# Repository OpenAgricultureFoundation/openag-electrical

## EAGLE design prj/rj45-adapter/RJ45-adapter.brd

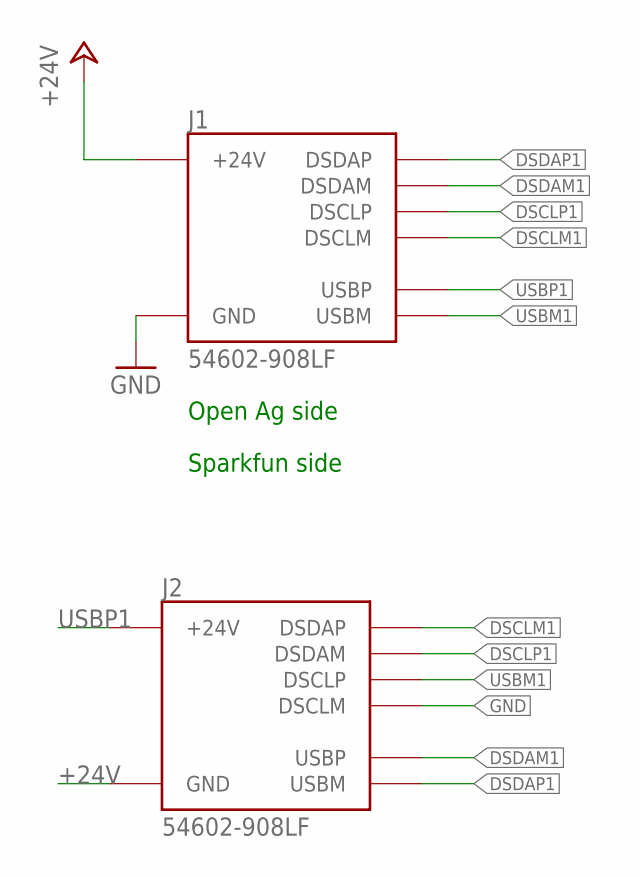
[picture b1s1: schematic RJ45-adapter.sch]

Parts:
J1, J2: 54602-908LF; OPENAG-V1-RJ45

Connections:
+24V: J1.24V(6) (+24V), J2.GND(3) (GND)
DSCLM1: J1.DSCLM(5) (DSCLM), J2.DSDAP(1) (DSDAP)
DSCLP1: J1.DSCLP(4) (DSCLP), J2.DSDAM(2) (DSDAM)
DSDAM1: J1.DSDAM(2) (DSDAM), J2.USBP(7) (USBP)
DSDAP1: J1.DSDAP(1) (DSDAP), J2.USBM(8) (USBM)
GND: J1.GND(3) (GND), J2.DSCLM(5) (DSCLM)
USBM1: J1.USBM(8) (USBM), J2.DSCLP(4) (DSCLP)
USBP1: J1.USBP(7) (USBP), J2.24V(6) (+24V)

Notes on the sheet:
Sparkfun side
Open Ag side

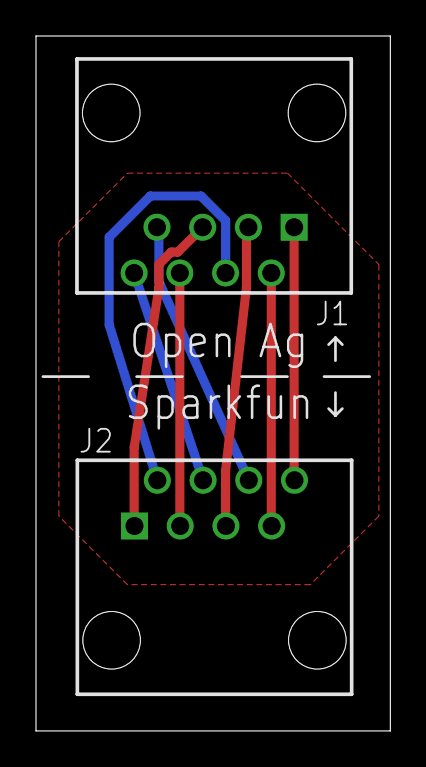
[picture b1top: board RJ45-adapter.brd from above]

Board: 2 copper layers, 19.7 x 38.6 mm, 3 parts (1 on the bottom side), 8 nets.

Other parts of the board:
ATTRIBUTES: DOCFIELD

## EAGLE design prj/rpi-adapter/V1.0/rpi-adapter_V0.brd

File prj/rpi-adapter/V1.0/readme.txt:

READ ME
Raspberry Pi to BBB socket i2c adapter 
THIS VERSION DOES NOT WORK! PLEASE SEE VERSION 2.0

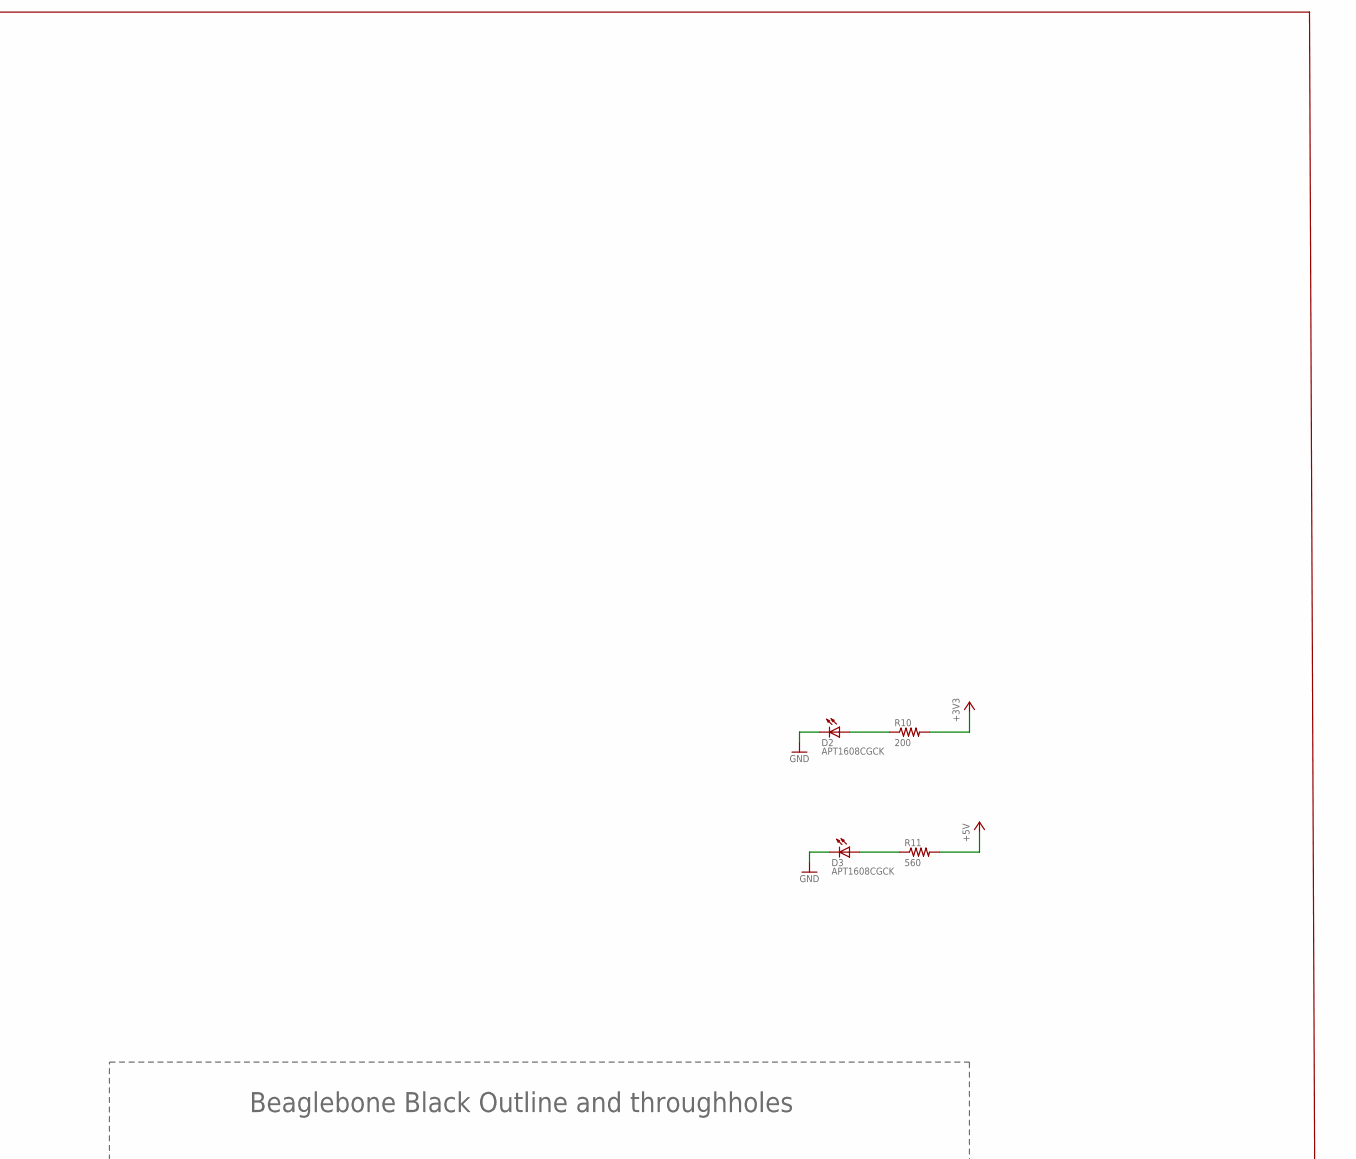
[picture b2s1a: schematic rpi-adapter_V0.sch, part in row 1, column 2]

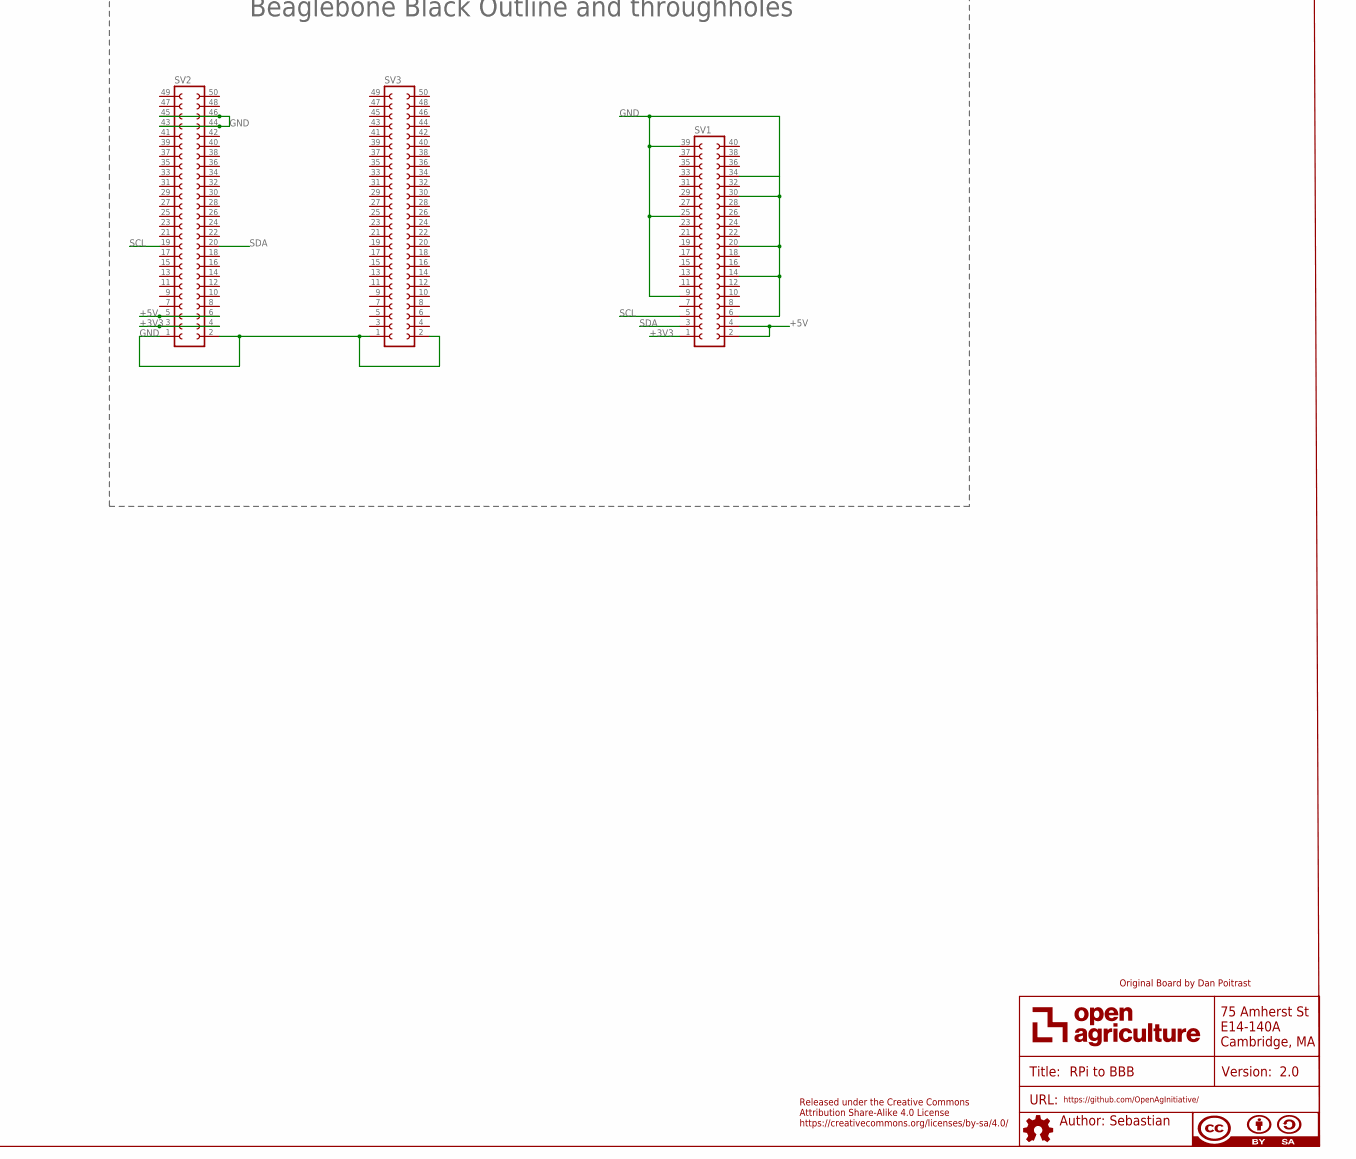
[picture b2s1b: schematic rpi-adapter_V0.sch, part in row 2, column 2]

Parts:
ATTRIBUTES: DOCFIELD
D2, D3: APT1608CGCK; CHIPLED_0603
R10: 200; RC0603N
R11: 560; RC0603N
SV1: FE20-2
SV2, SV3: FE25-2

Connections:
+3V3: R10.2, SV1.1, SV2.3, SV2.4
+5V: R11.2, SV1.2, SV1.4, SV2.5, SV2.6
GND: D2.C, D3.C, SV1.6, SV1.9, SV1.14, SV1.20, SV1.25, SV1.30, SV1.34, SV1.39, SV2.1, SV2.2, SV2.43, SV2.44, SV2.45, SV2.46, SV3.1, SV3.2
unnamed: D3.A, R11.1
unnamed: D2.A, R10.1
SCL: SV1.5, SV2.19
SDA: SV1.3, SV2.20

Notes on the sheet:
Original Board by Dan Poitrast
Released under the Creative Commons Attribution Share-Alike 4.0 License https://creativecommons.org/licenses/by-sa/4.0/
Beaglebone Black Outline and throughholes

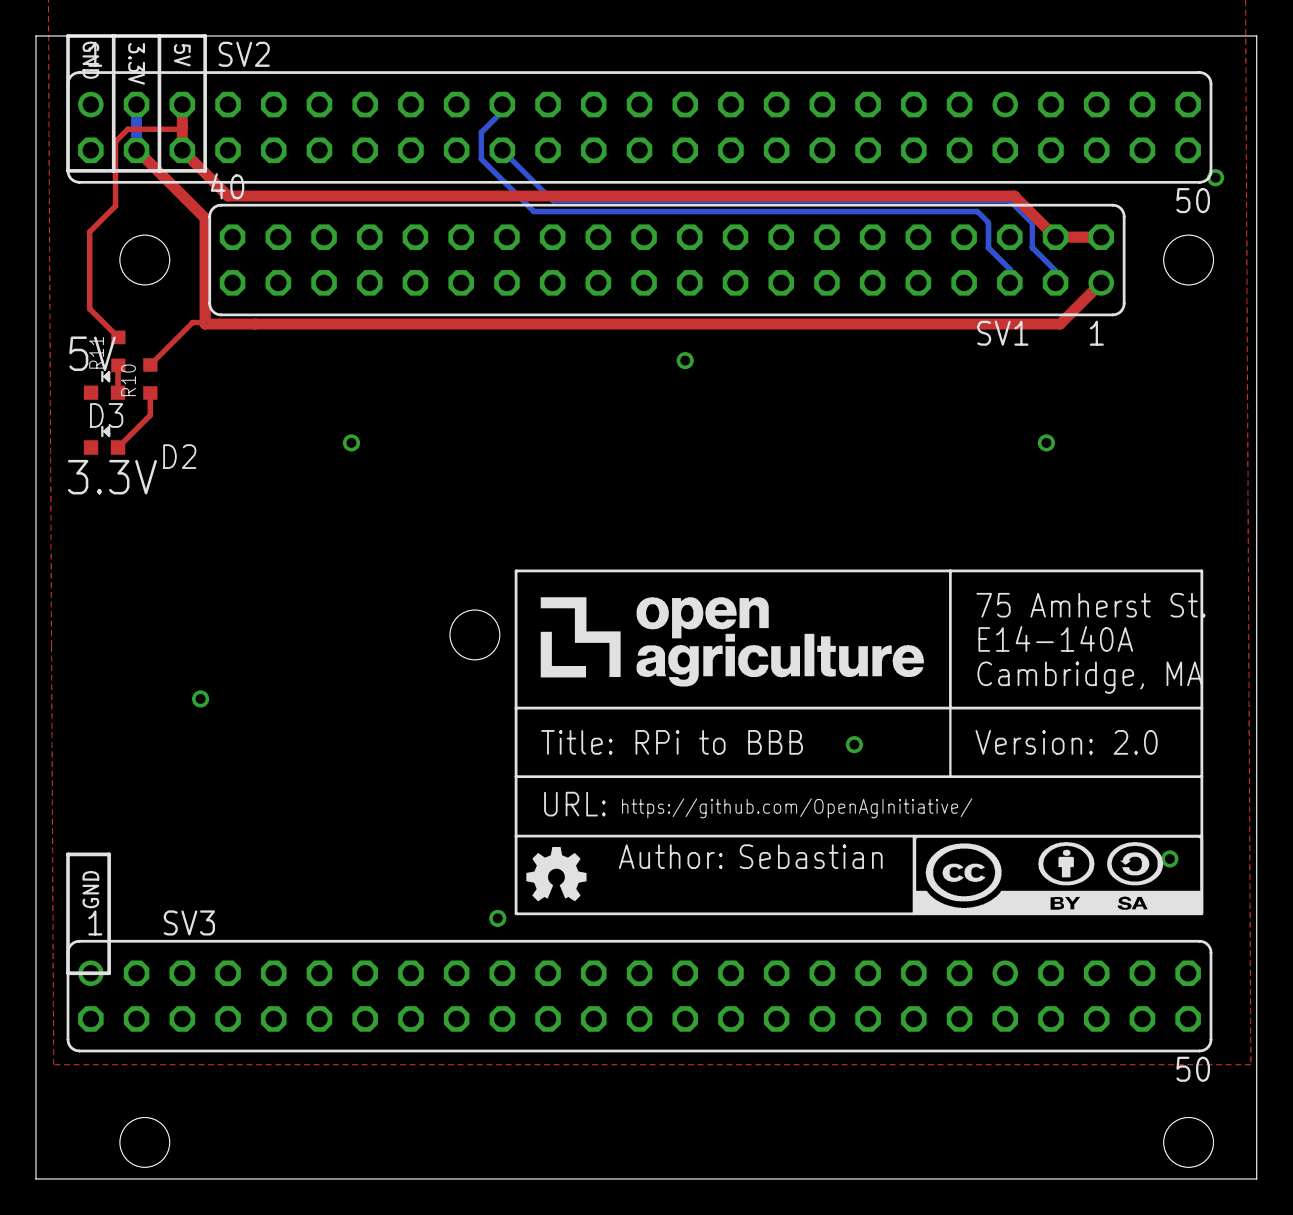
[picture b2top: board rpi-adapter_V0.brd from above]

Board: 2 copper layers, 67.8 x 63.5 mm, 8 parts (0 on the bottom side), 7 nets.

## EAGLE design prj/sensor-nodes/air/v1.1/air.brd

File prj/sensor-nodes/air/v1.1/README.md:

# Air Sensor Node v1.1
Sense air temperature, humidity and co2, redundently. Intended for evaluation purposes to determine sensors 
with best performance. Communicates over RJ45-dI2C for use with a nervous system board. Has option for standalone operation 
with wifi communication using a particle photon. Photon module has a 5v regulator enable to accomodate multiple power options. 
CO2 Sensors: T6713 and CCS811. Temperature / Humidity Sensors: SHT25 and HTU20DF.

### Contents
1. [Schematic](#schematic)
2. [Board](#board)
2. [Board Top](#board-top)
3. [Board Bottom](#board-bottom)
4. [Bill of Materials](air.csv)
5. [Gerber Files](air_sensor_node_v_1_1.zip)

### Schematic

### Board

### Board Top

### Board Bottom

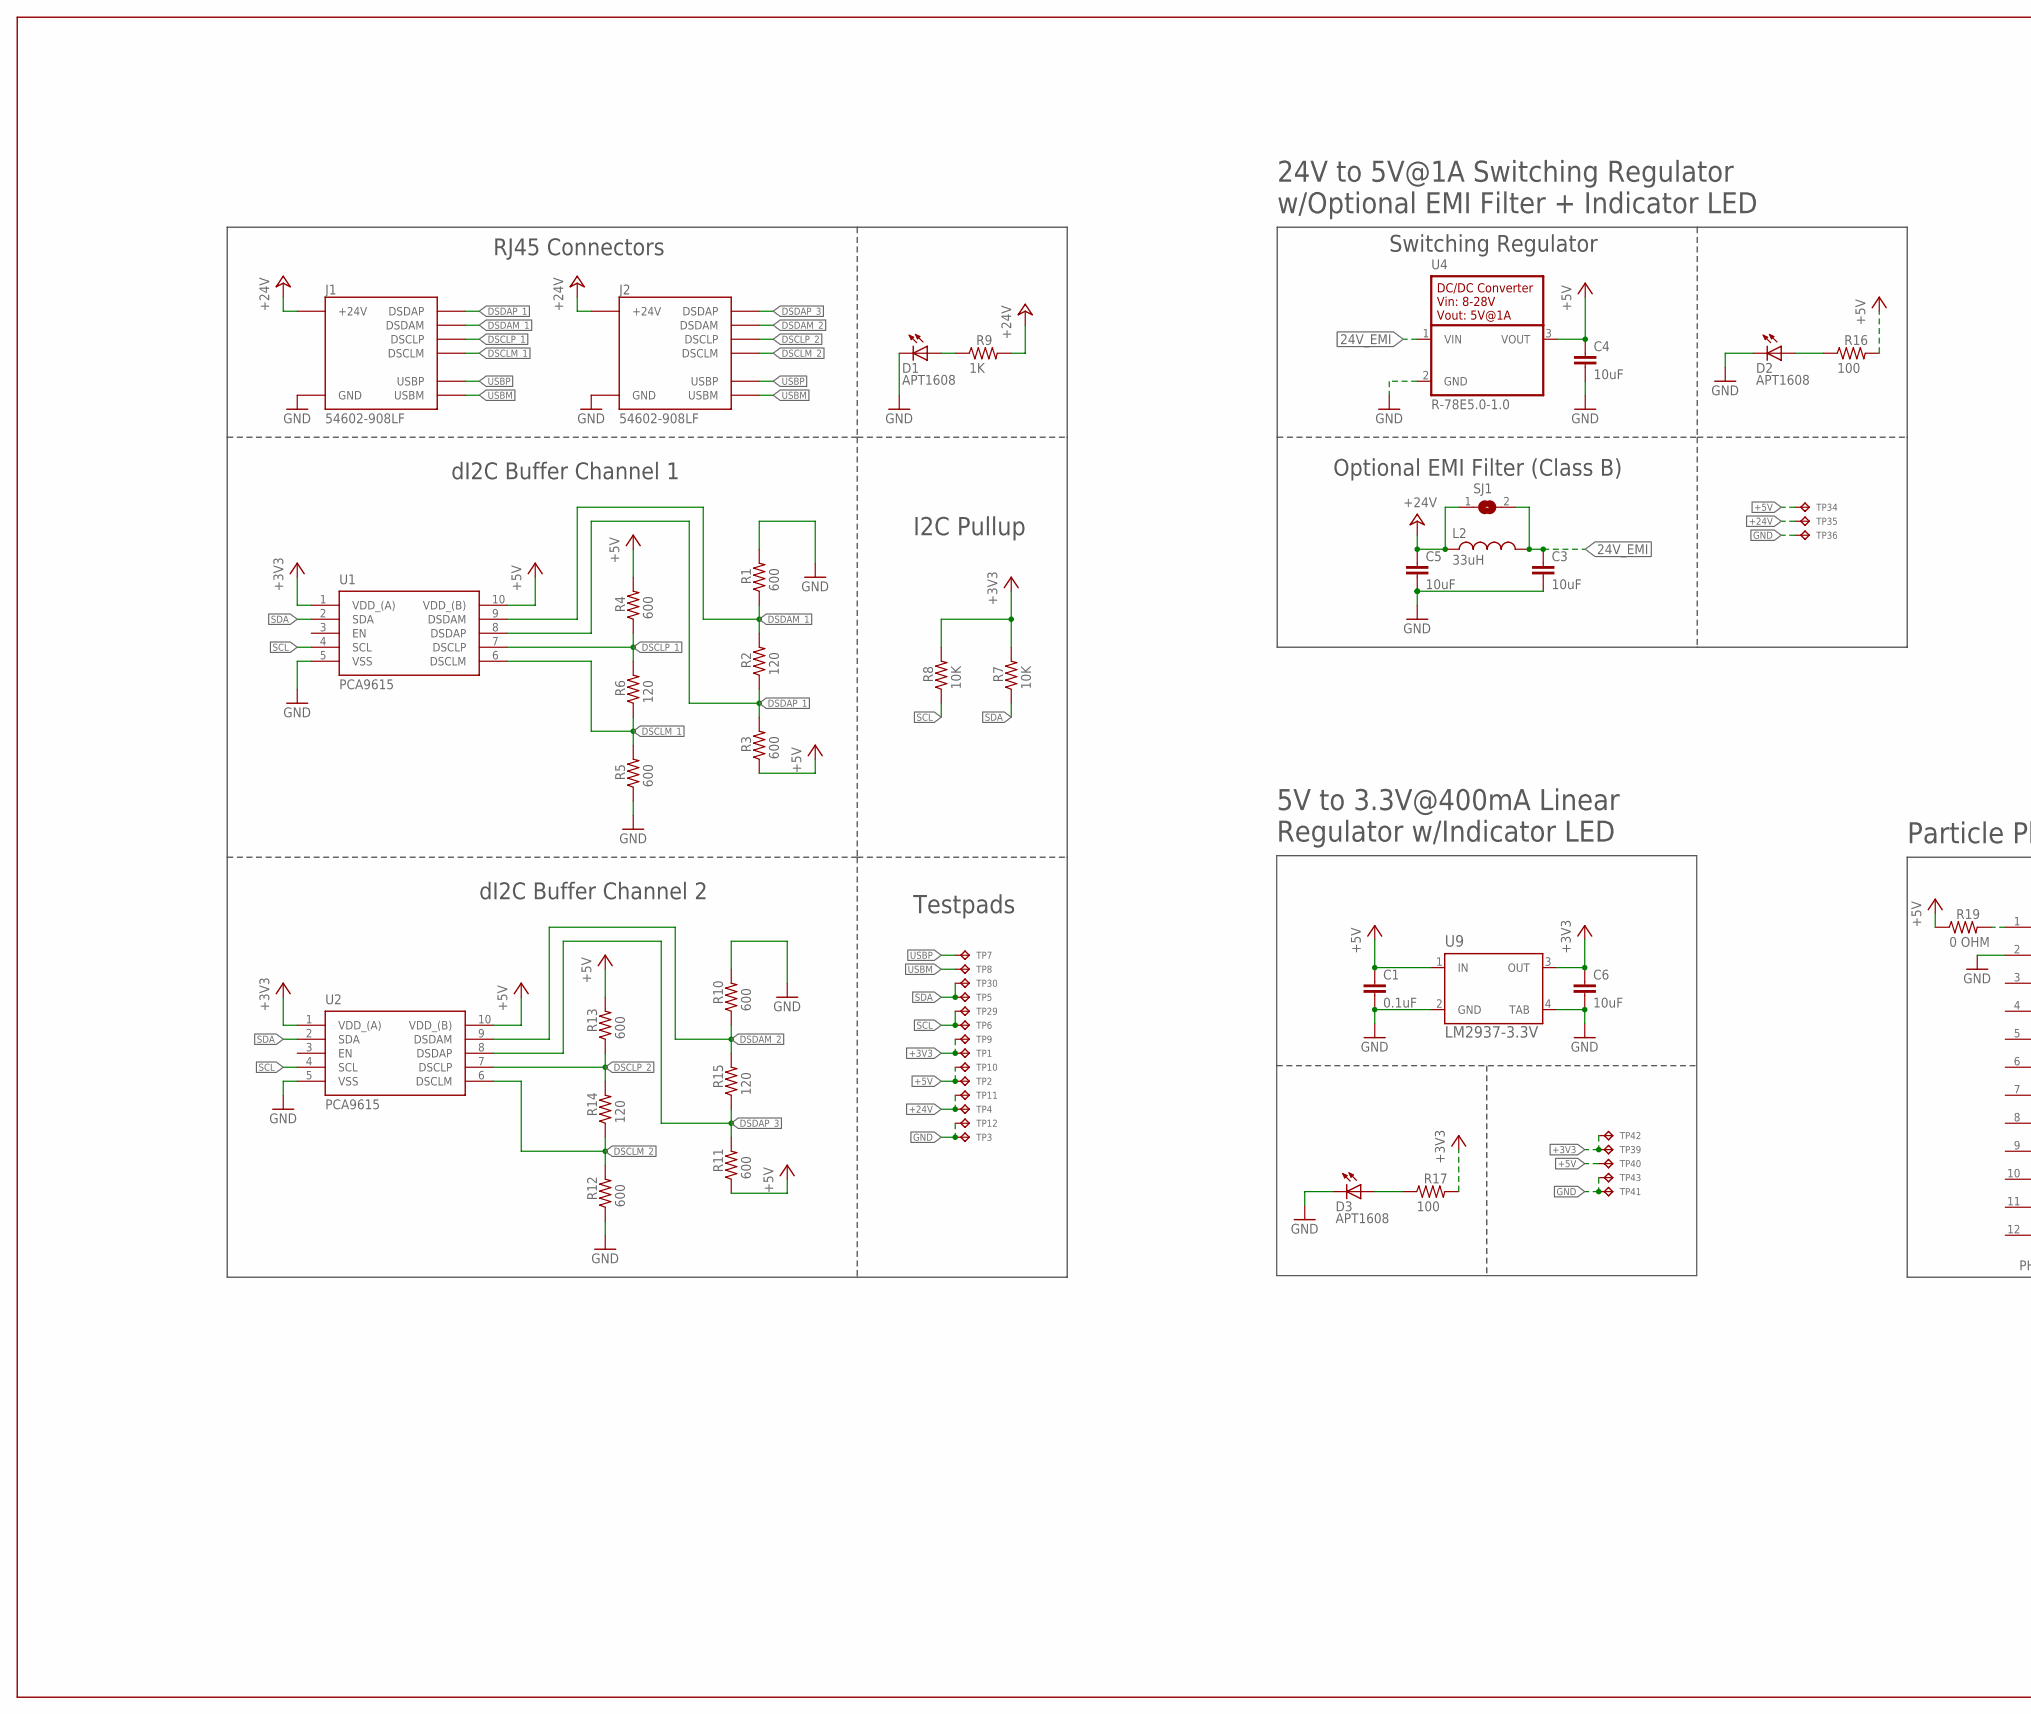
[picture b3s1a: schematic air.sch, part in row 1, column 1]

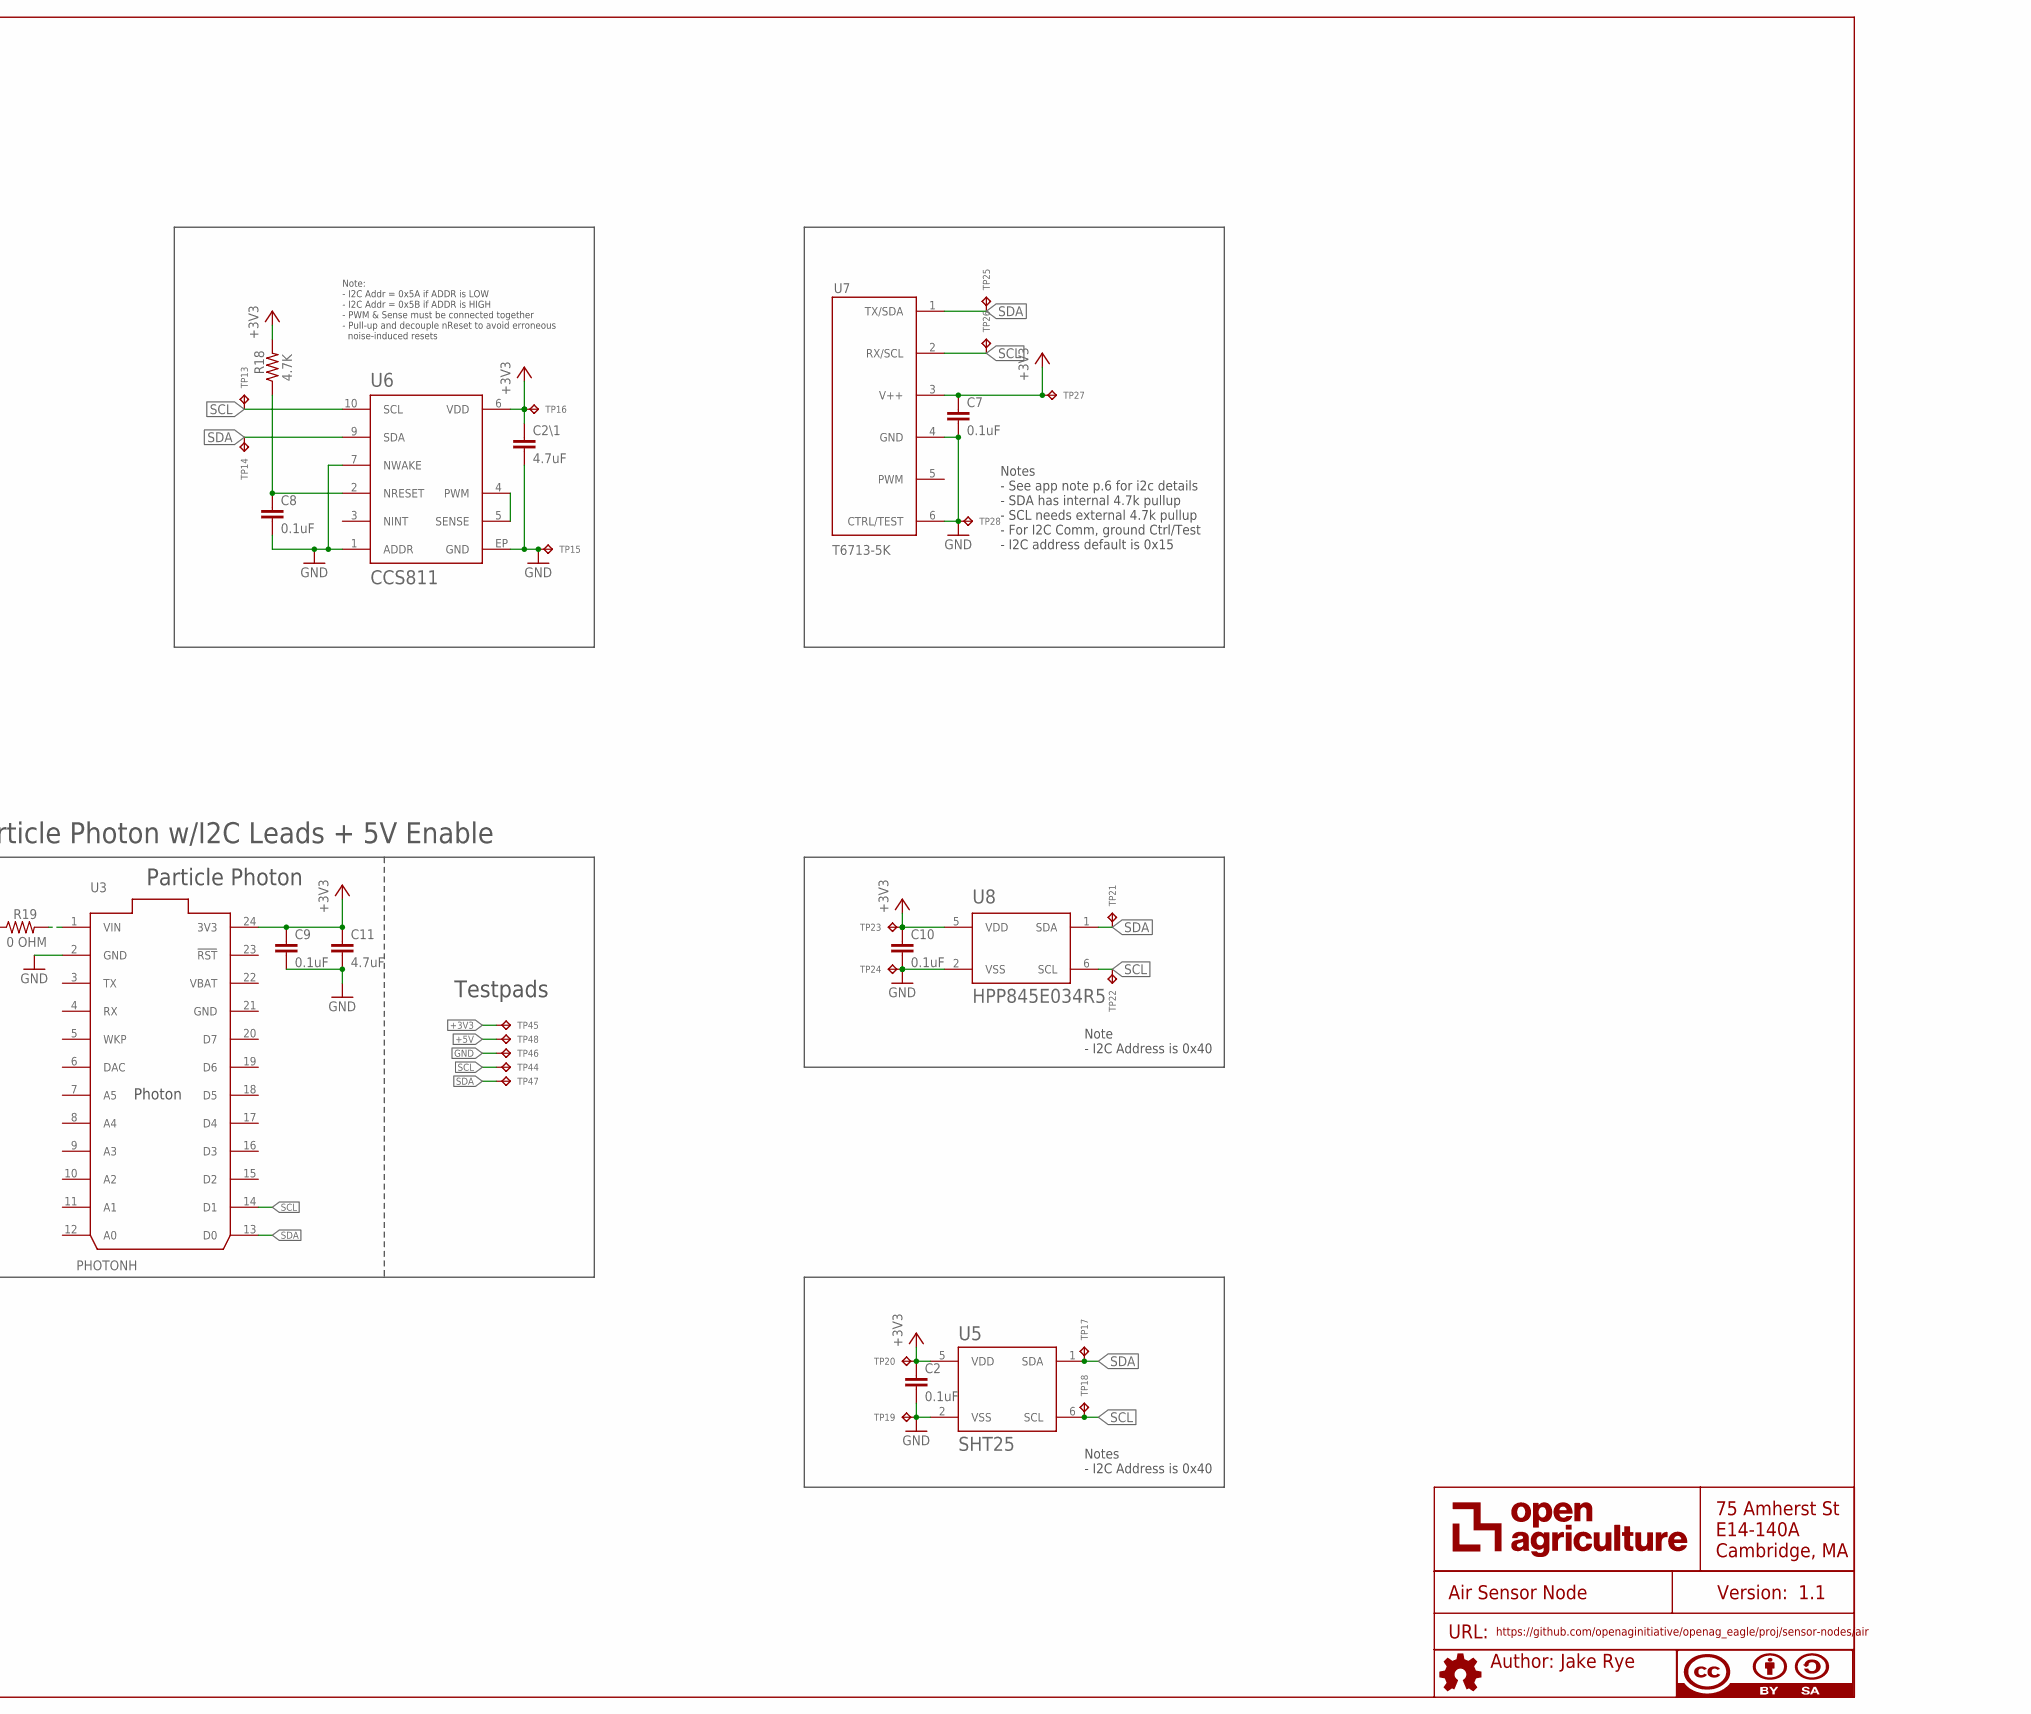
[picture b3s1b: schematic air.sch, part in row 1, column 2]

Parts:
C1, C2, C7, C8, C9, C10: 0.1uF; C0603
C2\1, C11: 4.7uF; C0805
C3, C4, C5, C6: 10uF; C0805
D1, D2, D3: APT1608; CHIPLED_0603
J1, J2: 54602-908LF; RJ45-DI2C-USB-54602-908LF
L2: 33uH; 29333C
R1, R3, R4, R5, R10, R11, R12, R13: 600; RC0603N
R2, R6, R14, R15: 120; RC0603N
R7, R8: 10K; RC0603N
R9: 1K; RC0603N
R16, R17: 100; RC0603N
R18: 4.7K; R1206
R19: 0 OHM; RC0603N
SJ1: EMI-BYPASS
TP1, TP2, TP3, TP4, TP5, TP6, TP7, TP8, TP9, TP10, TP11, TP12, TP29, TP30, TP39, TP40, TP41, TP42, TP43, TP44, TP45, TP46, TP47, TP48: TPTP04R; TP04R
TP13, TP14, TP15, TP16, TP17, TP18, TP19, TP20, TP21, TP22, TP23, TP24, TP25, TP26, TP27, TP28, TP34, TP35, TP36: TPTP06R; TP06R
U1, U2: PCA9615; SOP50P490X110-10N
U3: PHOTONH; PHOTON
U4: R-78E5.0-1.0
U5: SHT25; SHT2X
U6: CCS811
U7: T6713-5K; T6713
U8: HPP845E034R5; HTU20D(F)
U9: LM2937-3.3V; MP04A
U$1: AUTHOR
U$2: TITLE

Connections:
24V_EMI: C3.1, L2.2, SJ1.2, U4.1 (VIN)
+3V3: C2.1, C2\1.1, C6.1, C7.1, C9.1, C10.1, C11.1, R7.2, R8.2, R17.2, R18.2, TP1.1, TP9.1, TP16.TP, TP20.TP, TP23.TP, TP27.TP, TP39.1, TP42.1, TP45.1, U1.1 (VDD_(A)), U2.1 (VDD_(A)), U3.24 (3V3), U5.5 (VDD), U6.6 (VDD), U7.3 (V++), U8.5 (VDD), U9.3 (OUT)
+5V: C1.1, C4.1, R3.1, R4.2, R11.1, R13.2, R16.2, R19.1, TP2.1, TP10.1, TP34.TP, TP40.1, TP48.1, U1.10 (VDD_(B)), U2.10 (VDD_(B)), U4.3 (VOUT), U9.1 (IN)
+24V: C5.1, J1.24V(6) (+24V), J2.24V(6) (+24V), L2.1, R9.2, SJ1.1, TP4.1, TP11.1, TP35.TP
DSCLM_1: J1.DSCLM(5) (DSCLM), R5.2, R6.1, U1.6 (DSCLM)
DSCLM_2: J2.DSCLM(5) (DSCLM), R12.2, R14.1, U2.6 (DSCLM)
DSCLP_1: J1.DSCLP(4) (DSCLP), R4.1, R6.2, U1.7 (DSCLP)
DSCLP_2: J2.DSCLP(4) (DSCLP), R13.1, R14.2, U2.7 (DSCLP)
DSDAM_1: J1.DSDAM(2) (DSDAM), R1.1, R2.2, U1.9 (DSDAM)
DSDAM_2: J2.DSDAM(2) (DSDAM), R10.1, R15.2, U2.9 (DSDAM)
DSDAP_1: J1.DSDAP(1) (DSDAP), R2.1, R3.2, U1.8 (DSDAP)
DSDAP_3: J2.DSDAP(1) (DSDAP), R11.2, R15.1, U2.8 (DSDAP)
GND: C1.2, C2.2, C2\1.2, C3.2, C4.2, C5.2, C6.2, C7.2, C8.2, C9.2, C10.2, C11.2, D1.C, D2.C, D3.C, J1.GND(3) (GND), J2.GND(3) (GND), R1.2, R5.1, R10.2, R12.1, TP3.1, TP12.1, TP15.TP, TP19.TP, TP24.TP, TP28.TP, TP36.TP, TP41.1, TP43.1, TP46.1, U1.5 (VSS), U2.5 (VSS), U3.2 (GND), U3.21 (GND), U4.2 (GND), U5.2 (VSS), U6.1 (ADDR), U6.7 (NWAKE), U6.EP (GND), U7.4 (GND), U7.6 (CTRL/TEST), U8.2 (VSS), U9.2 (GND), U9.4 (TAB)
unnamed: D2.A, R16.1
unnamed: D3.A, R17.1
unnamed: D1.A, R9.1
unnamed: R19.2, U3.1 (VIN)
unnamed: U6.4 (PWM), U6.5 (SENSE)
unnamed: C8.1, R18.1, U6.2 (NRESET)
SCL: R8.1, TP6.1, TP13.TP, TP18.TP, TP22.TP, TP26.TP, TP29.1, TP44.1, U1.4 (SCL), U2.4 (SCL), U3.14 (D1), U5.6 (SCL), U6.10 (SCL), U7.2 (RX/SCL), U8.6 (SCL)
SDA: R7.1, TP5.1, TP14.TP, TP17.TP, TP21.TP, TP25.TP, TP30.1, TP47.1, U1.2 (SDA), U2.2 (SDA), U3.13 (D0), U5.1 (SDA), U6.9 (SDA), U7.1 (TX/SDA), U8.1 (SDA)
USBM: J1.USBM(8) (USBM), J2.USBM(8) (USBM), TP8.1
USBP: J1.USBP(7) (USBP), J2.USBP(7) (USBP), TP7.1
VBAT: U3.22 (VBAT)

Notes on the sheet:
Note: - I2C Addr = 0x5A if ADDR is LOW - I2C Addr = 0x5B if ADDR is HIGH - PWM & Sense must be connected together - Pull-up and decouple nReset to avoid erroneous noise-induced resets
Note - I2C Address is 0x40
Notes - I2C Address is 0x40
Notes - See app note p.6 for i2c details - SDA has internal 4.7k pullup - SCL needs external 4.7k pullup - For I2C Comm, ground Ctrl/Test - I2C address default is 0x15
24V to 5V@1A Switching Regulator w/Optional EMI Filter + Indicator LED
Switching Regulator
Optional EMI Filter (Class B)
dI2C Buffer Channel 1
RJ45 Connectors
dI2C Buffer Channel 2
Testpads
I2C Pullup
5V to 3.3V@400mA Linear Regulator w/Indicator LED
Particle Photon w/I2C Leads + 5V Enable
Particle Photon

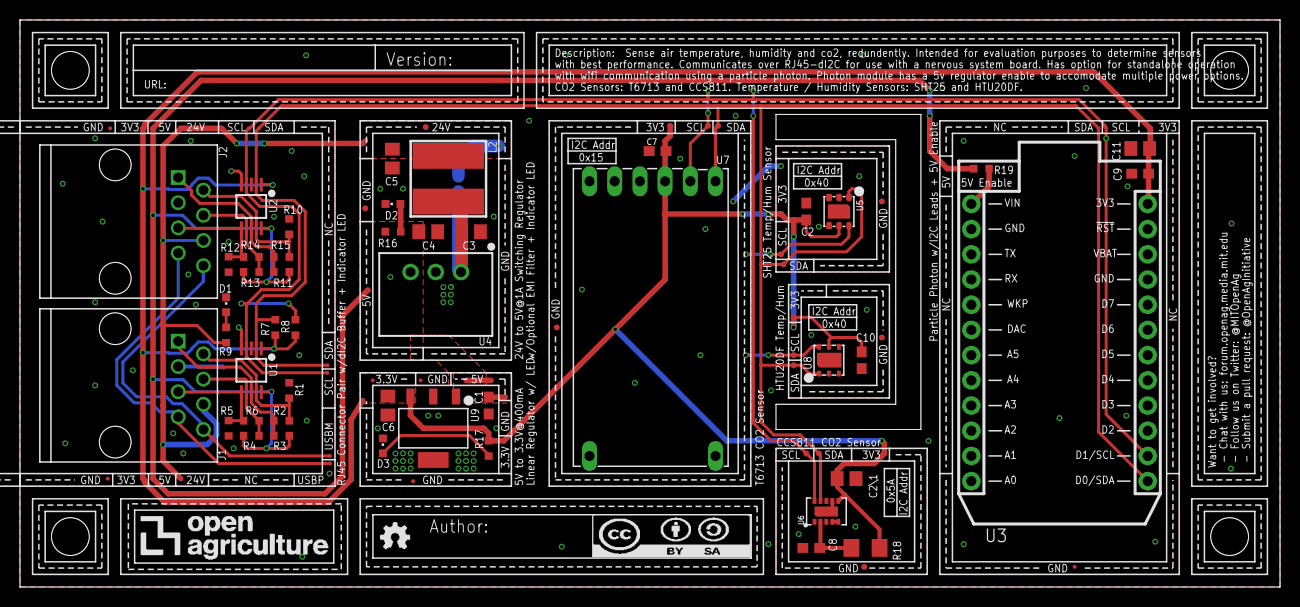
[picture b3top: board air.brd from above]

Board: 2 copper layers, 127.0 x 57.1 mm, 97 parts (1 on the bottom side), 23 nets.

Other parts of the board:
U$5: LOGO-900X300
U$6, U$7, U$8, U$9: CORNER-150

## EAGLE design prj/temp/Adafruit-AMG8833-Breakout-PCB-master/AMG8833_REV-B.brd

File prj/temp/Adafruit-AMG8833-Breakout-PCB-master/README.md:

# Adafruit-AMG8833-Breakout-PCB
PCB files for the Adafruit AMG8833 8x8 IR sensor breakout board

Format is EagleCAD schematic and board layout

For more details, check out the product page at

   * https://www.adafruit.com/products/3538

Adafruit invests time and resources providing this open source design, 
please support Adafruit and open-source hardware by purchasing 
products from Adafruit!

Designed by Adafruit Industries.  
Creative Commons Attribution, Share-Alike license, check license.txt for more information
All text above must be included in any redistribution

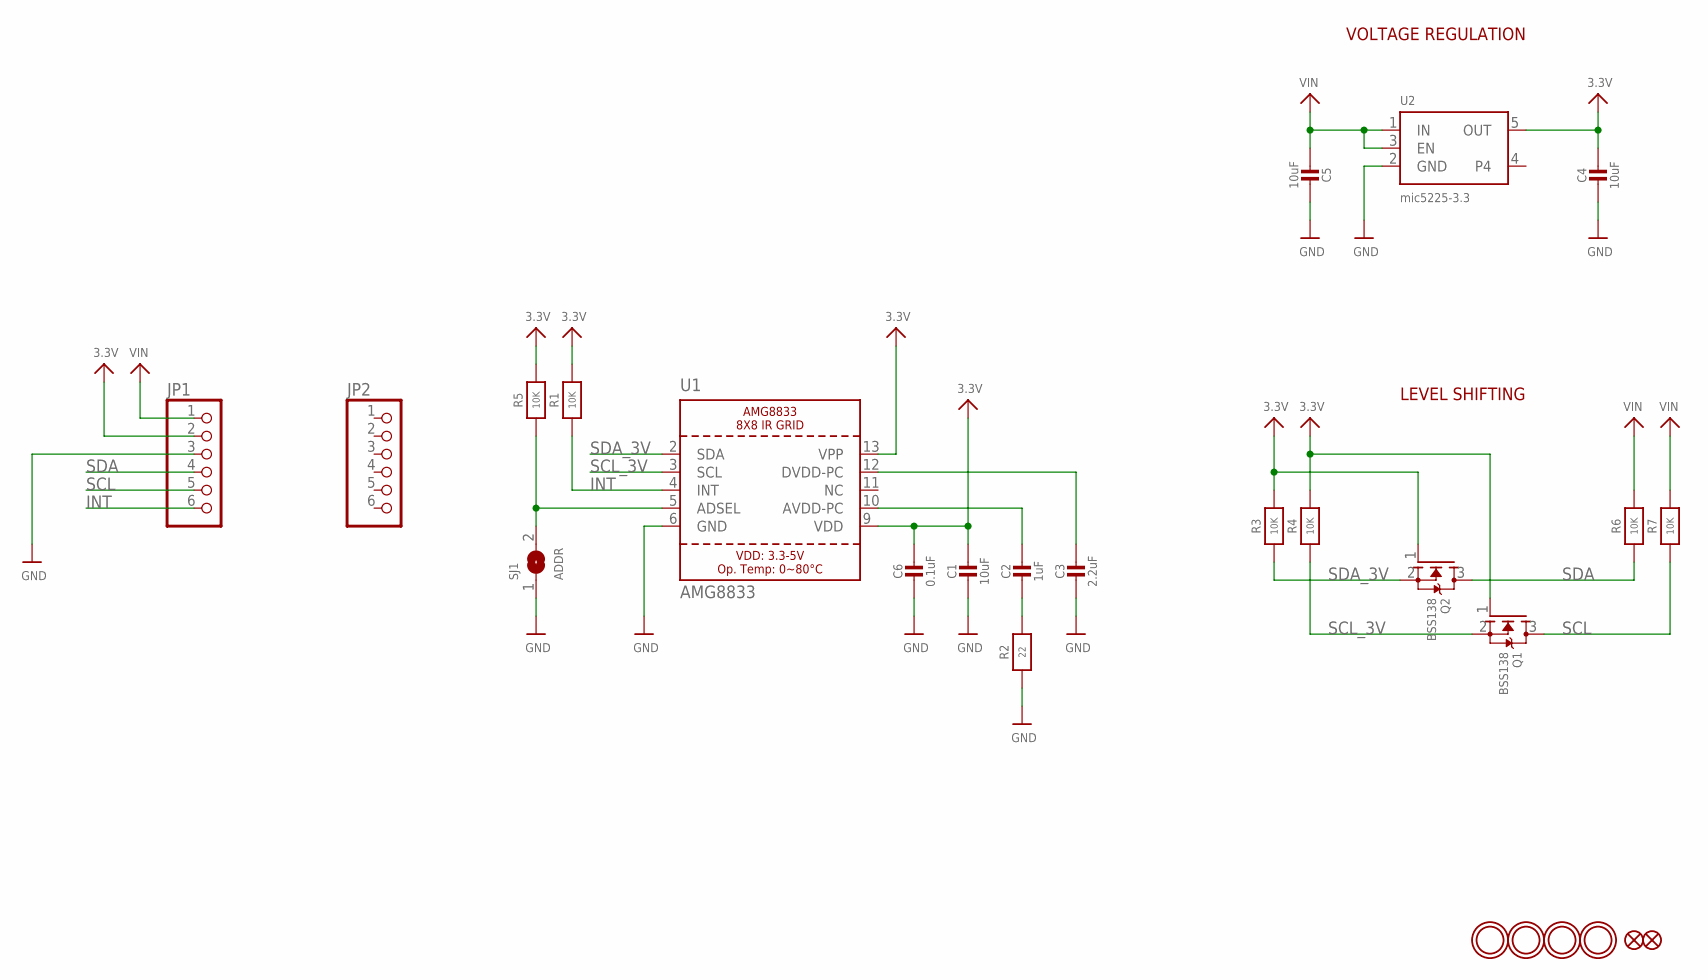
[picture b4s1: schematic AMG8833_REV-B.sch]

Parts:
C1, C4, C5: 10uF; 0805-NO
C2: 1uF; 0805-NO
C3: 2.2uF; 0805-NO
C6: 0.1uF; 0805-NO
FID2, FID3: FIDUCIAL_1MM
JP1, JP2: HEADER-1X670MIL; 1X06_ROUND_70
Q1, Q2: BSS138; SOT23-WIDE
R1, R3, R4, R5: 10K; 0805-NO
R2: 22; 0805-NO
R6, R7: 10K; 0805_10MGAP
SJ1: ADDR; SOLDERJUMPER_ARROW_NOPASTE
U1: AMG8833
U2: mic5225-3.3; SOT23-5
U$16, U$17, U$18, U$19: MOUNTINGHOLE2.5; MOUNTINGHOLE_2.5_PLATED

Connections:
3.3V: C1.1, C4.1, C6.1, JP1.2, Q1.1 (G), Q2.1 (G), R1.2, R3.2, R4.2, R5.2, U1.9 (VDD), U1.13 (VPP), U2.5 (OUT)
AVDD-PC: C2.1, U1.10 (AVDD-PC)
DVDD-PC: C3.1, U1.12 (DVDD-PC)
GND: C1.2, C3.2, C4.2, C5.1, C6.2, JP1.3, R2.1, SJ1.1, U1.6 (GND), U2.2 (GND)
INT: JP1.6, R1.1, U1.4 (INT)
unnamed: R5.1, SJ1.2, U1.5 (ADSEL)
unnamed: C2.2, R2.2
SCL: JP1.5, Q1.3 (D), R7.1
SCL_3V: Q1.2 (S), R4.1, U1.3 (SCL)
SDA: JP1.4, Q2.3 (D), R6.1
SDA_3V: Q2.2 (S), R3.1, U1.2 (SDA)
VIN: C5.2, JP1.1, R6.2, R7.2, U2.1 (IN), U2.3 (EN)

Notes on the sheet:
VOLTAGE REGULATION
LEVEL SHIFTING

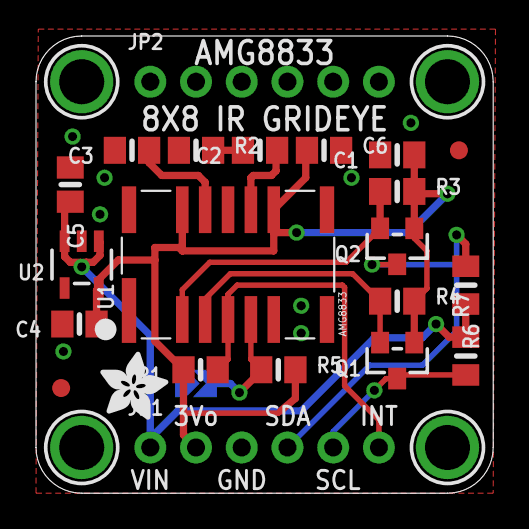
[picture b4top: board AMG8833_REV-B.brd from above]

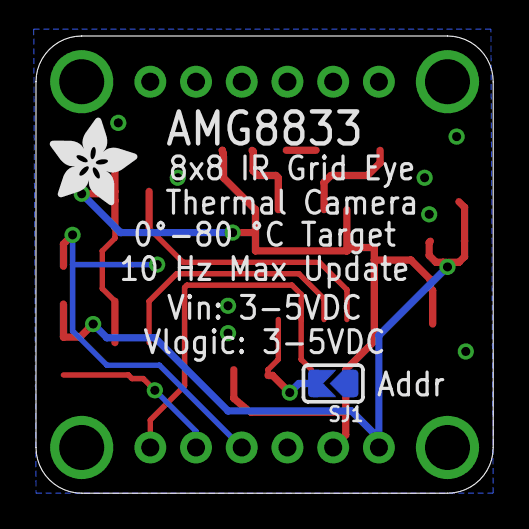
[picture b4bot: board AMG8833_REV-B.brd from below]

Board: 2 copper layers, 25.4 x 25.4 mm, 28 parts (2 on the bottom side), 12 nets.

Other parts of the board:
U$21: ADAFRUIT_3.5MM
U$28: ADAFRUIT_5MM

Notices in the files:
parts and their libraries:
microbuilder: This work is placed in the public domain, and may be freely used for commercial and non-commercial work with the following conditions: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
